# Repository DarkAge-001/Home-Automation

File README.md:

# Home-Automation
IoT home improves convenience, security, and enery efficiency, making homes smarter and more efficient.
This repo contains some major IoT home automation files including Microcontroller Schematics, firmware and PCB designs.
Some of the Key features in this repository include:
1.  Central Hub design: Uisng ESP32 microcontroller, a PCB was designed for a temperature & humidity sensor module that communicates with the central hub to pass across data of the sensor. 
2.  Automation & Control for Lighting: A circuit was designed using Arduino to control LED strip based on ambient light levels using an LDR sensor. This circuit was designed using Proteus 8 professional software and simulated as well.
3.  Security: A Motion Security feature was implemented using PIR motion sensor to trigger an alarm system when motion is detected. simulated and designed using Proteus.
4.  Energy Management: It optimize power consumption for the device by implementing Sleep modes.

NOTE: All codes(Firmware) is written in C++ using Arduino IDE. The schematic designs and Simulations are carried out using Proteus 8 professional software. The PCB design was carried out using KICAD software.

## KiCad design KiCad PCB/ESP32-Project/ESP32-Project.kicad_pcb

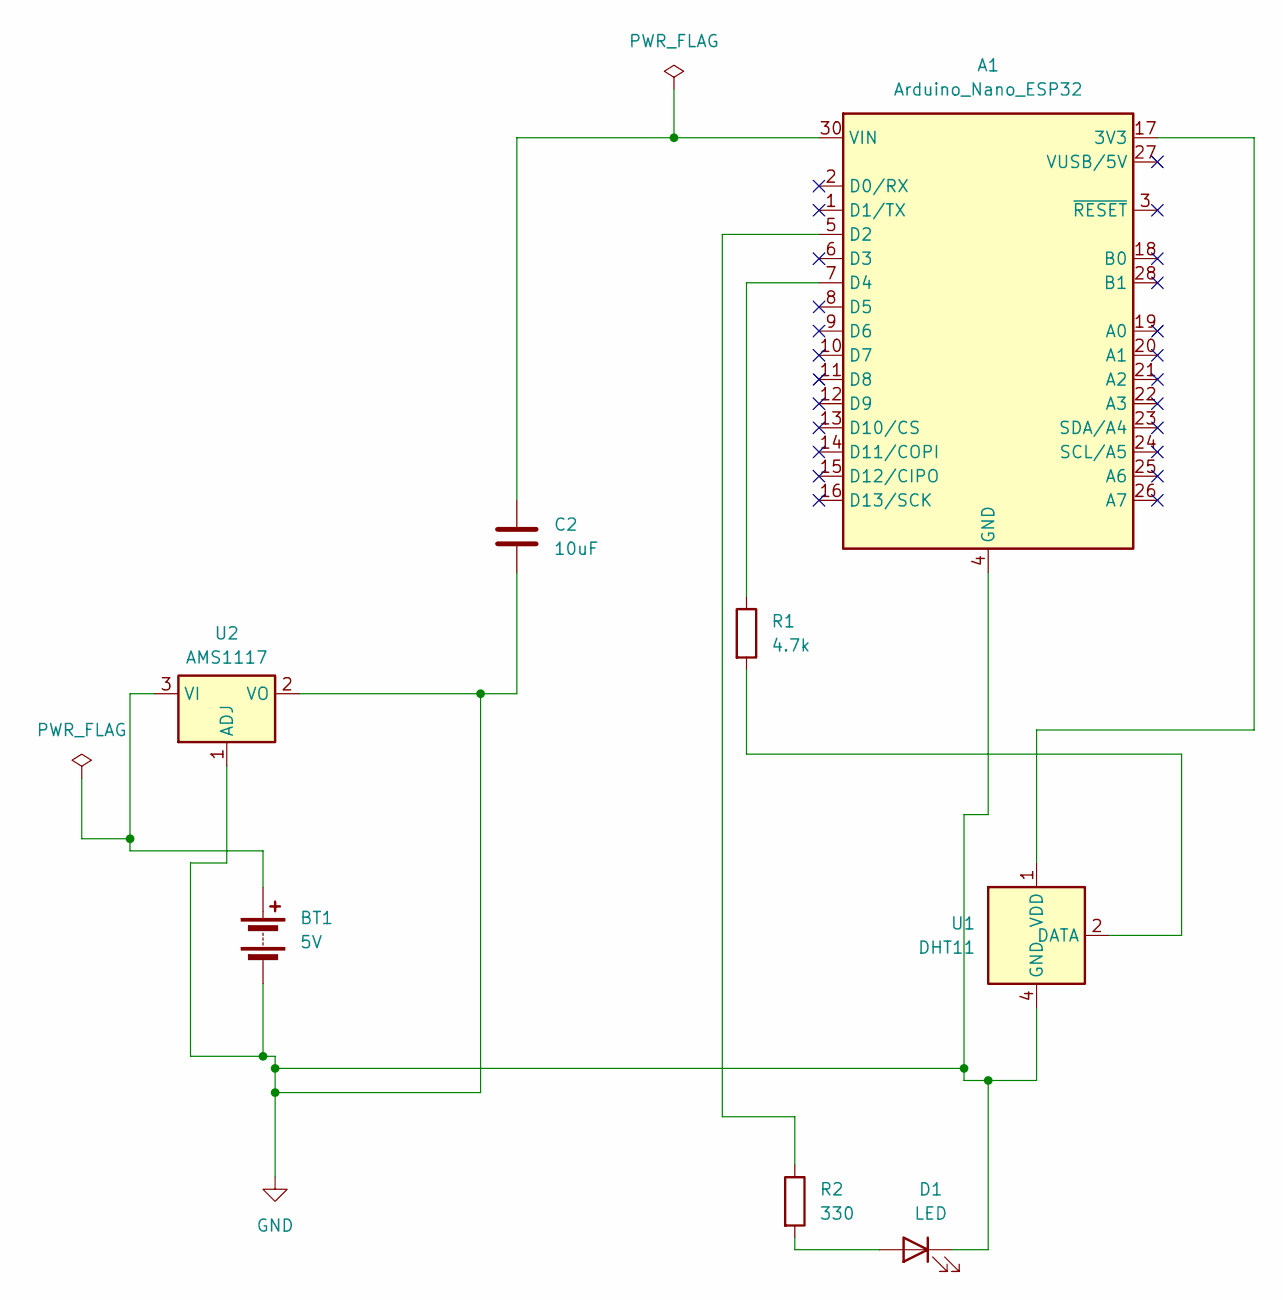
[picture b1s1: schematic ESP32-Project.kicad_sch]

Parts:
A1: Arduino_Nano_ESP32; Arduino_Nano
BT1: 5V; BatteryHolder_Keystone_2462_2xAA
C2: 10uF; CP_Elec_5x3
D1: LED; LED_D4.0mm
R1: 4.7k; R_Axial_DIN0204_L3.6mm_D1.6mm_P7.62mm_Horizontal
R2: 330; R_Axial_DIN0204_L3.6mm_D1.6mm_P7.62mm_Horizontal
U1: DHT11; Aosong_DHT11_5.5x12.0_P2.54mm
U2: AMS1117; SOT-223-3_TabPin2

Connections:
GND: A1.4 (GND), A1.29 (GND), BT1.2 (-), C2.2, D1.1 (K), U1.4 (GND), U2.1 (ADJ), U2.2 (VO)
unnamed: A1.17 (3V3), U1.1 (VDD)
unnamed: A1.5 (D2), R2.1
unnamed: A1.7 (D4), R1.1
unnamed: A1.30 (VIN), C2.1
unnamed: BT1.1 (+), U2.3 (VI)
unnamed: D1.2 (A), R2.2
unnamed: R1.2, U1.2 (DATA)

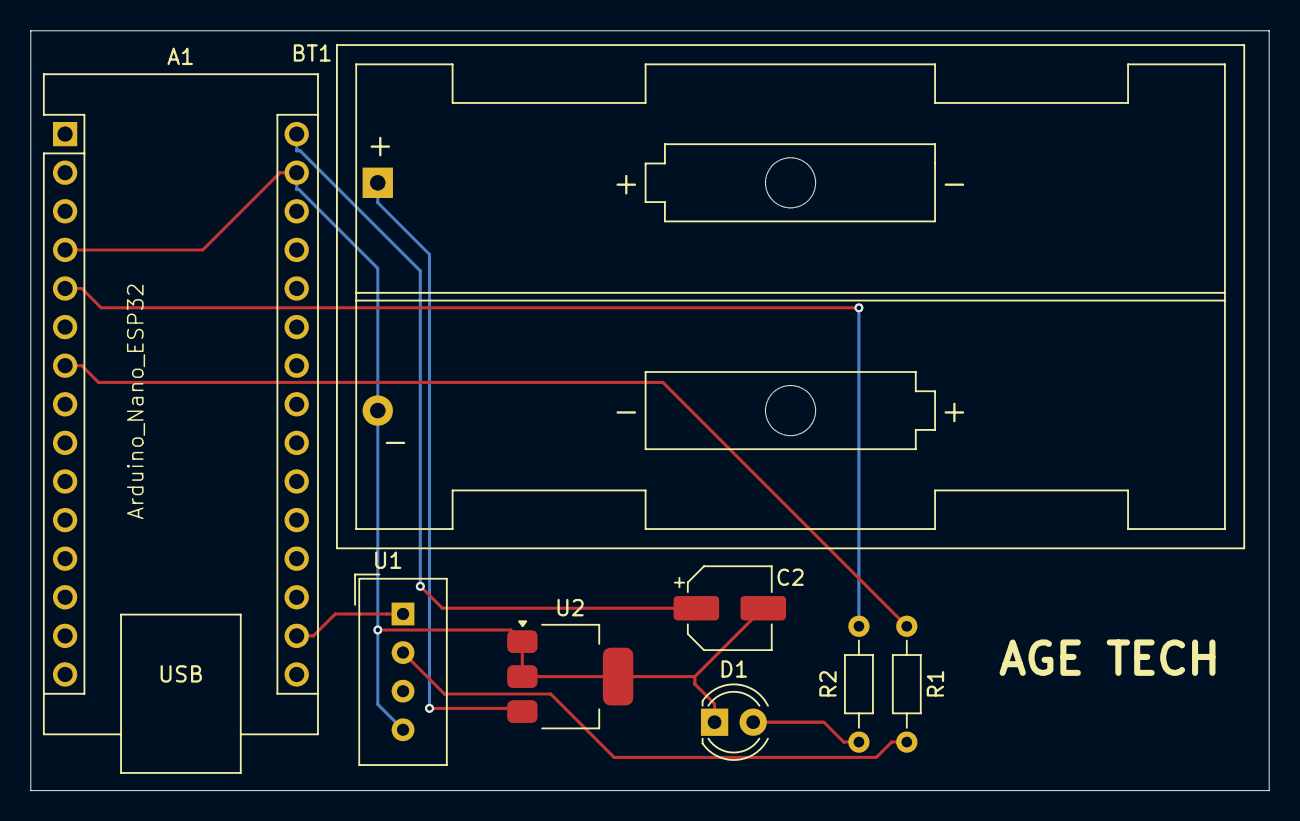
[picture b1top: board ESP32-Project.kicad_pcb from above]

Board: 2 copper layers, 81.5 x 50.0 mm, 8 parts (0 on the bottom side), 8 nets.
